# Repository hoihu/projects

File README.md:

# projects
General embedded projects

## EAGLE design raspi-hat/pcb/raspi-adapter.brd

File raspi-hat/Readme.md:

# Raspberry/HAT <-> Pyboard adapter

There's a large range of addon boards available for the raspberry pi (called "HAT") but not a lot for the micropython reference board ([Pyboard](https://micropython.org/store/#/products/PYBv1_1)). 

Using this adapter PCB it's possible to connect a PyBoard to a HAT extension board. HAT's are extension PCBs that plug into the 40pin connector of a raspberry Pi - they are cheap and a lot of them readily available by distributors (e.g. [Adafruit](https://www.adafruit.com/category/286)). So it would be a great addition to the MicroPython environment if they can be reused by the Pyboard!

While the main intention was to use existing HAT's where the pyboard acts like a raspberry, it's also possible to use the board the other way round: The  pyboard can then talk to a raspberry and emulate a HAT device.

## Physical
Example stackup: SenseHat on top of Interface board (pink). Pyboard sits below interface board but can also be placed on top of it if space is sufficient.

## What's a HAT?
Specification of the HAT's are [here](https://github.com/raspberrypi/hats).

In short, they must fulfill the mechanical dimensions provided and contain an I2C EEPROM with information about the serial number, GPIO setup and linux device tree. At boot time, the raspberry checks this configuration and configures the GPIO accordingly. See [here](https://www.disk91.com/2015/technology/hardware/design-a-raspberry-pi-hat-shield/) of how an EEPROM image can be created.

In principle, a HAT can use most of the wires that the 40pin connector provides. However most HATs use the UART, SPI or I2C, together with some other GPIOs of the first 28 pins.

## Adapter PCB HW configurations
The adapter board allows to interface a pyboard with the 40pin header of a raspberry. 2 configurations are supported:

* attach a HAT to the 40pin connector and use the pyboard as master device. This means the pyboard acts like a raspberry and controls a HAT. Solder a 40pin MALE connecter to the top side of the adapter board.
* attach a Raspi to the 40pin connector and use the pyboard as slave device. It means the pyboard acts like a HAT and listens to commands from the raspberry. Solder a 40pin FEMALE connector on the bottom side of the adapter board.

In addition the adapter PCB contains:

* An I2C-EEPROM which can be useful if you want to develop a fully HAT compatible board with the pyboard. It's mandatory by the foundation that only an I2C EEPROM can be attached to pin 27/28, however it might be possible that the pyboard can act as I2C slave so the EEPROM becomes obsolete? That's one of the many questions that this adapter should help to answer.
* A FET driver circuit to drive external neopixel strips. The neopixel can be driven by the SPI output of the pyboard. There is a jumper that allows the supply of the neopixel to be applied externally (separate power supply) or internally (using the +5V USB).
* 2 buttons for RST and DFU -> so it's easy to update your pyboard firmware.
* (FTDI) Headers for UART/I2C access of the pyboard. So it's easy to debug and log outputs from the pyboard on the PC

## PCB

The outline follows the official requirements by the raspberry foundation. 

The pyboard can be placed above or below the board - depending on how you want to place the HAT or how you have mounted the headers on the pyboard. 

As a special feature, the area where the pyboard is socketed contains no VIA's. This way it's possible to solder the pyboard directly to the adapter board without causing a short.

It might be that a HAT will overlap the pyboard and there is not enought room in between. In that case it's preferred to place the pyboard on the bottom side.

The 40pin connector can either be a male type (in case you want to access a HAT) or a female type (if you use it as a HAT togehter with a raspi).

### GPIO connection
Most of the 40pin GPIOs and the most important interfaces (UART/SPI/I2C) are wired to the pyboard. The follwing table gives an overview:

| Pyboard Pin   | GPIO (pin)    |
| ------------- |:-------------:|
| X10           | SDA (3)       |
| X9            | SCL (5)       |
| Y4            | GPIO4 (7)     |
| X3            | GPIO17 (11)   |
| Y3            | GPIO18 (12)   |
| X4            | GPIO27 (13)   |
| Y11           | GPIO22 (15)   |
| Y12           | GPIO25 (16)   |
| X5            | GPIO24 (18)   | 
| Y8            | MOSI (19)     | 
| Y7            | MISO (21)     |
| X12           | GPIO25 (22)   | 
| Y6            | CLK (23)      | 
| Y5            | SS (24)       |
| X11           | GPIO7 (26)    | 
| Y10           | SDA_ID (27)   | 
| Y9            | SCL_ID (28)   | 
| LED_BLUE      | GPIO19 (35)   | 
| LED_YELLOW    | GPIO20 (38)   | 
| LED_GREEN     | GPIO21 (40)   |

See also the schematic for details.

I checked some commonly used HAT's and the setup above should allow to control most of them (most use only the first 28pins).

### Jumper configurations
#### HAT configuration (pyboard controls a HAT attached to the 40pin connector)
place the jumper as follows:

* JP5/JP6 (at the top left) vertically
* JP2 inserted (3V3 provided by Pyboard)

#### Raspberry configuration (pyboard acts like a HAT that is attached to a raspberry via the 40pin connector)
place the jumper as follows:

* JP5/JP6 horizontally
* Attention: DO *NOT* insert JP2 (3V3 is given by the Raspberry)

#### Advanced options:
* Remote reset (raspberry can control reset line of pyboard): place JP4/JP1 vertically, otherwise horizontally (see also schematic for details). That might be a nice option if a raspberry was used to auto-test a pyboard?
* The pyboards internal LED states (the yellow/green/blue one) are available on the GPIO header pins 35,38,40. So a raspberry Pi can check if a reset is pending etc. Also that could be useful for automated test cases.

## How to use it
### To connect a HAT to the pyboard
#### ID EEPROM readout and ATOM parser
[ideeprom.py](ideeprom.py) gives an example on how to reads the internal EEPROM of the HAT and interpret data information like vendor,product serial. They are structured in so-called ATOM binary blobs. In principle, that should work on any HAT board but I've tested it only on the SenseHAT so far.

#### Pyboard as Master device, use HAT as a shield
As an example, I added basic support for the [SenseHAT](https://www.raspberrypi.org/products/sense-hat/) that supports
- LED matrix with/without scrolling in any directions
- LED matrix text display (with and without scrollin), 
- joystick read (up/down/left/right,pressed events), 
- temperature of both of pressure and humidity sensor
- pressure readout of barometric sensor
- humidity readout
- ..and IMU readout (accelerometer, gyroscope and magnetometer)!

Overview 
```
                SenseHAT Board
                +-+-+-+-+-+-+-+-+-+-+-+-+-+-+-+-+-+-+-+-+-+-+-+-+-+-+
                |                                                   |
I2c master  -------------> HTS21 (Humidity/Temp  @ addr 0x5f)       +
(RPi/Pyboard)   |  |                                                |
                +  |-----> LPS25H (Pressure/Temp @ addr 0x5c)       +
                |  |                                                |
                +  |-----> LSM9DS1 (9DOF IMU     @ addr 0x1c, 0x6a) +
                |  |                                                |
                +  |-----> 8x8 RGB LED Matrix &                     +
                |          Joystick Keys (Atmel  @ addr 0x46)       |
                +-+-+-+-+-+-+-+-+-+-+-+-+-+-+-+-+-+-+-+-+-+-+-+-+-+-+
```
the drivers are divided into single python files ([atmel.py](atmel.py), [lps25.py](lps25.py), [hts21.py](hts21.py), [LSM9DS1](lsm9ds1.py) so they can be reused.
 
[sensehat.py](sensehat.py) is a helper to configure all drivers automatically for the SenseHAT board
 
Example usage (on serial REPL)
```python
Example usage:
>>> from sensehat import uSenseHAT
>>> sense = uSenseHAT(I2C(1, I2C.MASTER))
>>> sense.matrix.write("Hi Micropython")   # scrolling text on LED matrix
>>> sense.matrix.set_pixel(4,4,(20,20,0))  # set pixel (4,4) to color (20,20,0)
>>> sense.read_humidity()   # humidty in percent rH
58.25
>>> sense.read_temperature()      # returns average temperature from HTS21 & LPS25 sensors
21.2213
>>> sense.read_pressure()   # returns hPa
970.8609
>>> sense.read_key()        # returns key state (pressed, left,right etc)
0
>>> sense.read_imu()       # returns raw value of gyro, accelerometer, magnetometer
((-0.4037476, 0.8224488, -0.05233765), (-0.009338379, 0.07415771, 0.9942017), 
(0.5358887, -0.001586914, -0.1228027))
```

See also Youtube Videos:
[here](https://www.youtube.com/watch?v=PeZRtHPF3iU) and [here](https://www.youtube.com/watch?v=LYzvXsxPtbw)

It would be nice to use the TFT HAT's but that's probably a bigger challenge and might needs c-level framebuffer support which is apparently in development.

## How to get the board?
A first batch was manufactured at OSH Park and released as a shared project. You can order it [here](https://oshpark.com/shared_projects/iNvYGvMJ). Note that 3 boards cost around 54$ (it's a 4 layer design hence it's a more expensive than a 2 layer design)

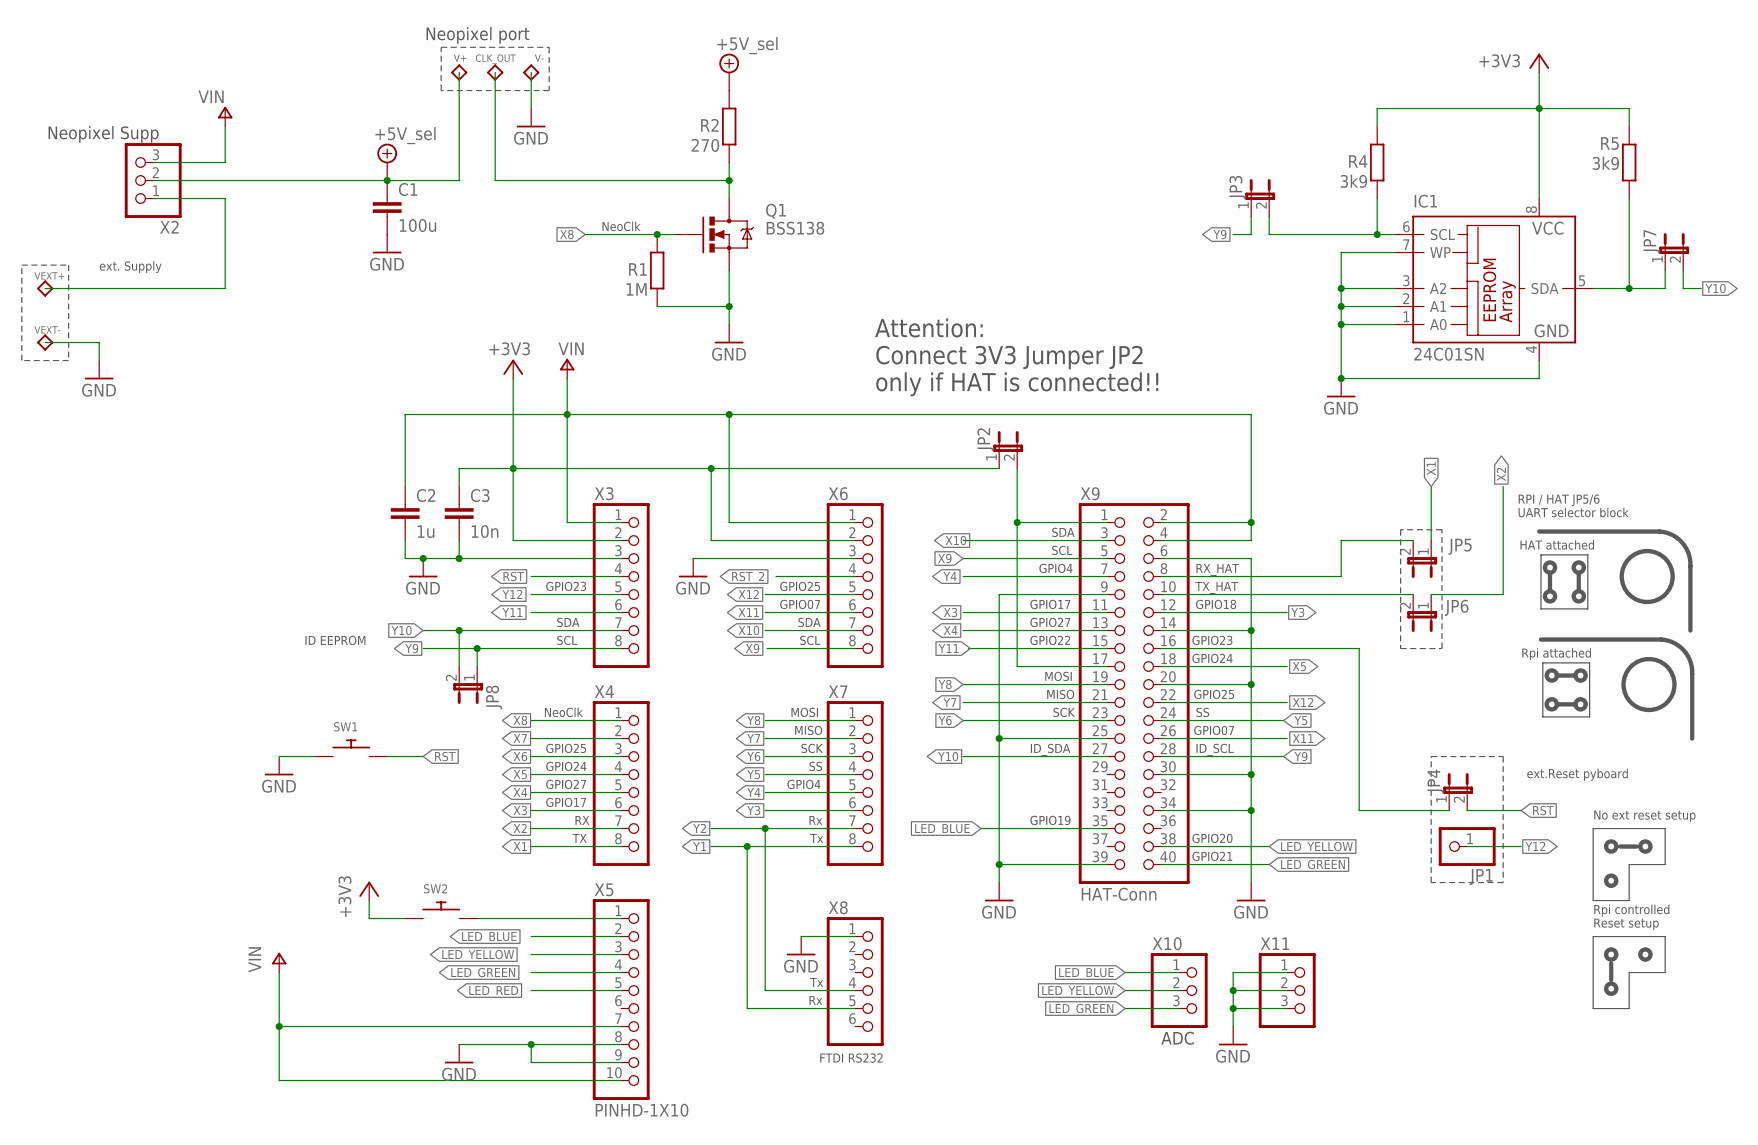
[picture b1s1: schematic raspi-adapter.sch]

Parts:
C1: 100u; C2220K
C2: 1u; C0603
C3: 10n; C0603
CLK_OUT: TP_BATT; TP_BATT_GROSS
IC1: 24C01SN; SO-08
JP1: PINHD-1X1; 1X01
JP2, JP3, JP4, JP5, JP6, JP7, JP8: JUMPER-2PTH; 1X02
Q1: BSS138; SOT23
R1: 1M; R0603
R2: 270; R0603
R4, R5: 3k9; R0603
SW1, SW2: SWITCH_PUSHBUTTONSOFTTOUCHSMD_SJ; PUSHBUTTON_SMD_SJ
V+: V+; TP_BATT_GROSS
V-: TP_BATT; TP_BATT_GROSS
VEXT+: TP_BATT; TP_BATT_GROSS
VEXT-: TP_BATT; TP_BATT_GROSS
X2, X10, X11: PINHD-1X3; 1X03
X3, X4, X6, X7: PINHD-1X8CLEANBIG; 1X08-CLEANBIG
X5: PINHD-1X10; 1X10-BIG
X8: PINHD-1X6B; 1X06-BIG
X9: HAT-Conn; 2X20

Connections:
3V3_RPI: JP2.2, X9.1, X9.17
+3V3: C3.1, IC1.8 (VCC), JP2.1, R4.2, R5.2, SW2.P$1, X3.2, X6.2
+5V: C1.1, R2.2, V+.1, X2.2
GND: C1.2, C2.2, C3.2, IC1.1 (A0), IC1.2 (A1), IC1.3 (A2), IC1.4 (GND), IC1.7 (WP), Q1.2 (S), R1.1, SW1.P$1, V-.1, VEXT-.1, X3.3, X5.8, X5.9, X6.3, X8.1, X9.6, X9.9, X9.14, X9.20, X9.25, X9.30, X9.34, X9.39, X11.1, X11.2, X11.3
LED_BLUE: X5.2, X9.35, X10.1
LED_GREEN: X5.4, X9.40, X10.3
LED_RED: X5.5
LED_YELLOW: X5.3, X9.38, X10.2
unnamed: VEXT+.1, X2.1
unnamed: SW2.P$2, X5.1
unnamed: CLK_OUT.1, Q1.3 (D), R2.1
unnamed: JP4.1, X9.16
RST: JP4.2, SW1.P$2, X3.4
RST_2: X6.4
SCL: IC1.6 (SCL), JP3.2, R4.1
SDA: IC1.5 (SDA), JP7.1, R5.1
V+: C2.1, X2.3, X3.1, X6.1, X9.2, X9.4
VIN: X5.7, X5.10
X1: JP5.1, X4.8
X1_: JP5.2, X9.8
X2: JP6.1, X4.7
X2_2: JP6.2, X9.10
X3: X4.6, X9.11
X4: X4.5, X9.13
X5: X4.4, X9.18
X6: X4.3
X7: X4.2
X8: Q1.1 (G), R1.2, X4.1
X9: X6.8, X9.5
X10: X6.7, X9.3
X11: X6.6, X9.26
X12: X6.5, X9.22
Y1: X7.8, X8.5
Y2: X7.7, X8.4
Y3: X7.6, X9.12
Y4: X7.5, X9.7
Y5: X7.4, X9.24
Y6: X7.3, X9.23
Y7: X7.2, X9.21
Y8: X7.1, X9.19
Y9: JP3.1, JP8.1, X3.8, X9.28
Y10: JP7.2, JP8.2, X3.7, X9.27
Y11: X3.6, X9.15
Y12: JP1.1, X3.5

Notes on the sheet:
MOSI
MISO
SCK
RX_HAT
TX_HAT
SDA
SCL
ID_SDA
ID_SCL
ID EEPROM
GPIO4
GPIO18
GPIO17
GPIO27
GPIO22
ext.Reset pyboard
RPI / HAT JP5/6 UART selector block
ext. Supply
GPIO20
GPIO21
GPIO19
FTDI RS232
ADC
GPIO24
GPIO07
GPIO25
NeoClk
HAT attached
Rpi attached
GPIO23
Neopixel port
Neopixel Supp
Attention: Connect 3V3 Jumper JP2 only if HAT is connected!!
No ext reset setup
Rpi controlled Reset setup

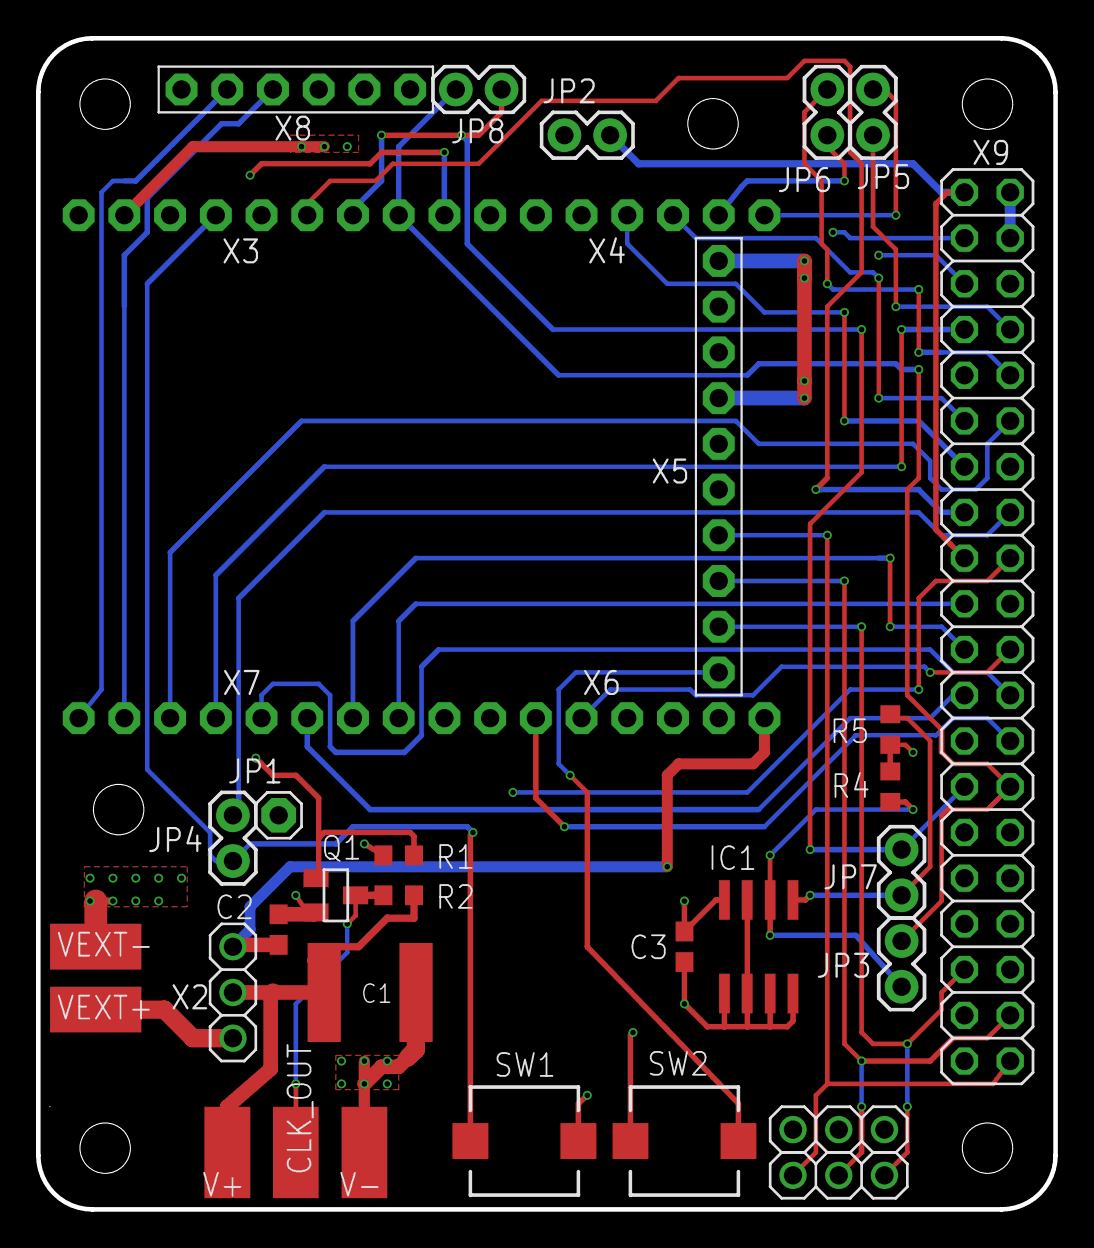
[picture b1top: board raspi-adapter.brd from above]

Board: 4 copper layers, 56.5 x 65.1 mm, 34 parts (0 on the bottom side), 40 nets.

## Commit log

2015-10-23 import cdc example
2015-10-23 added micropython submodule
2015-10-23 added examples files for CDC
2015-10-26 cube 1.3.0 CDC example for regulus
2015-10-26 removed old files
2015-10-31 cdc standalone using STM's cube library
2015-10-31 removed build folder
2015-10-31 improved callbacks, no more using TIM counter, instead rely on USB polling from host with a callback
2015-10-31 cdc polling interval set to 10msec
2015-10-31 cdc example with reading 1 char and output a multple of it (demonstrates tx/rx via CDC) - of course without TIM ;)
2015-11-01 cdc with ringbuffer, working
2015-11-01 cdc with ringbuffer, cleanup
2015-11-01 added missing files
2015-11-02 working ringbuffer with cdc rx
2015-11-02 yes - working uPy prompt ;)
2015-11-06 repl not yet working (string output are blcoking)
2015-11-09 UART added
2015-11-11 added printf support
2015-11-12 working repl, more less..
2015-11-18 changes in ringbuffer, stmhal
2015-12-18 debug files
2016-01-01 added testscript for CDC pyboard
2016-01-12 added raspi adapter files
2016-01-16 review schematic and layout
2016-01-17 working in review, removed onboard neopixel
2016-01-31 readme
2016-02-07 changed pics
2016-02-07 using multi-read mode of LPS sensor
2016-02-08 added humidity support for HTS221 of sensehat
2016-02-12 added hts temperature readout
2016-02-12 memoryview objects for temperature calculations
2016-02-12 sensehat driver improvements
2016-02-12 docu updates
2016-02-12 picture update - thanks to zsquareplusc
2016-02-13 doc updates
2016-02-13 separate files for lps,hts sensors
2016-02-13 added scrolling support for sensehat
2016-02-14 fixed point support added
2016-02-14 working text scrolling on sensehat
2016-02-14 added missing file, new output of temp,rh,pressure
2016-02-14 doc updates, some fixes
2016-02-14 added main.py
2016-02-14 doc update
2016-02-14 fixed main.py
2016-03-23 working magnetometer
2016-03-23 added prelimenary gyro driver
2016-03-23 working accelerator scaling
2016-03-23 added working IMU
2016-03-23 working ball example
2016-03-23 readme content
2016-03-25 cleanup
2016-03-31 working ball example
    readme content
2016-03-31 removed properties
2016-05-13 docker: added files
2016-05-13 docker: docu updates
2016-08-15 fusion.py: add link for upstream repository
2016-08-30 upy: added ajax example, worked with adafruit huzzah
2016-08-30 docker: fixes builds, added scripts
2016-09-19 docker: updated dockerfiles
2016-09-19 lsm9ds1: updated to new machine API
    untested so far
2016-09-29 uPy: add example for home wifi and neopixel
2016-12-02 upy(limi): add test scripts
2016-12-04 Add not about upstream repo
2017-05-09 uPy/jupyter: add initial docs
2017-07-10 hts221: driver updates
2017-07-10 hts221: using ucstruct
2017-07-10 hts221: RFC sensor implementation start
2017-07-18 hts221: adapted to new API, WIP
2017-08-17 fix: made drivers working again with machine API
2017-08-17 fix: main.py and sensehat.py examples
2017-08-17 added fritzing wiring example with pyboard
2017-11-12 add backofen files
2018-09-07 add odroid support example
2021-02-20 add example of dma transfer and uctypes dma lib
2021-02-21 add ws2812 dma example
2021-02-21 changed doc
2022-05-01 Successfully tested on LED strip

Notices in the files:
parts and their libraries:
SparkFun-Passives: Licensing: Creative Commons ShareAlike 4.0 International - https://creativecommons.org/licenses/by-sa/4.0
